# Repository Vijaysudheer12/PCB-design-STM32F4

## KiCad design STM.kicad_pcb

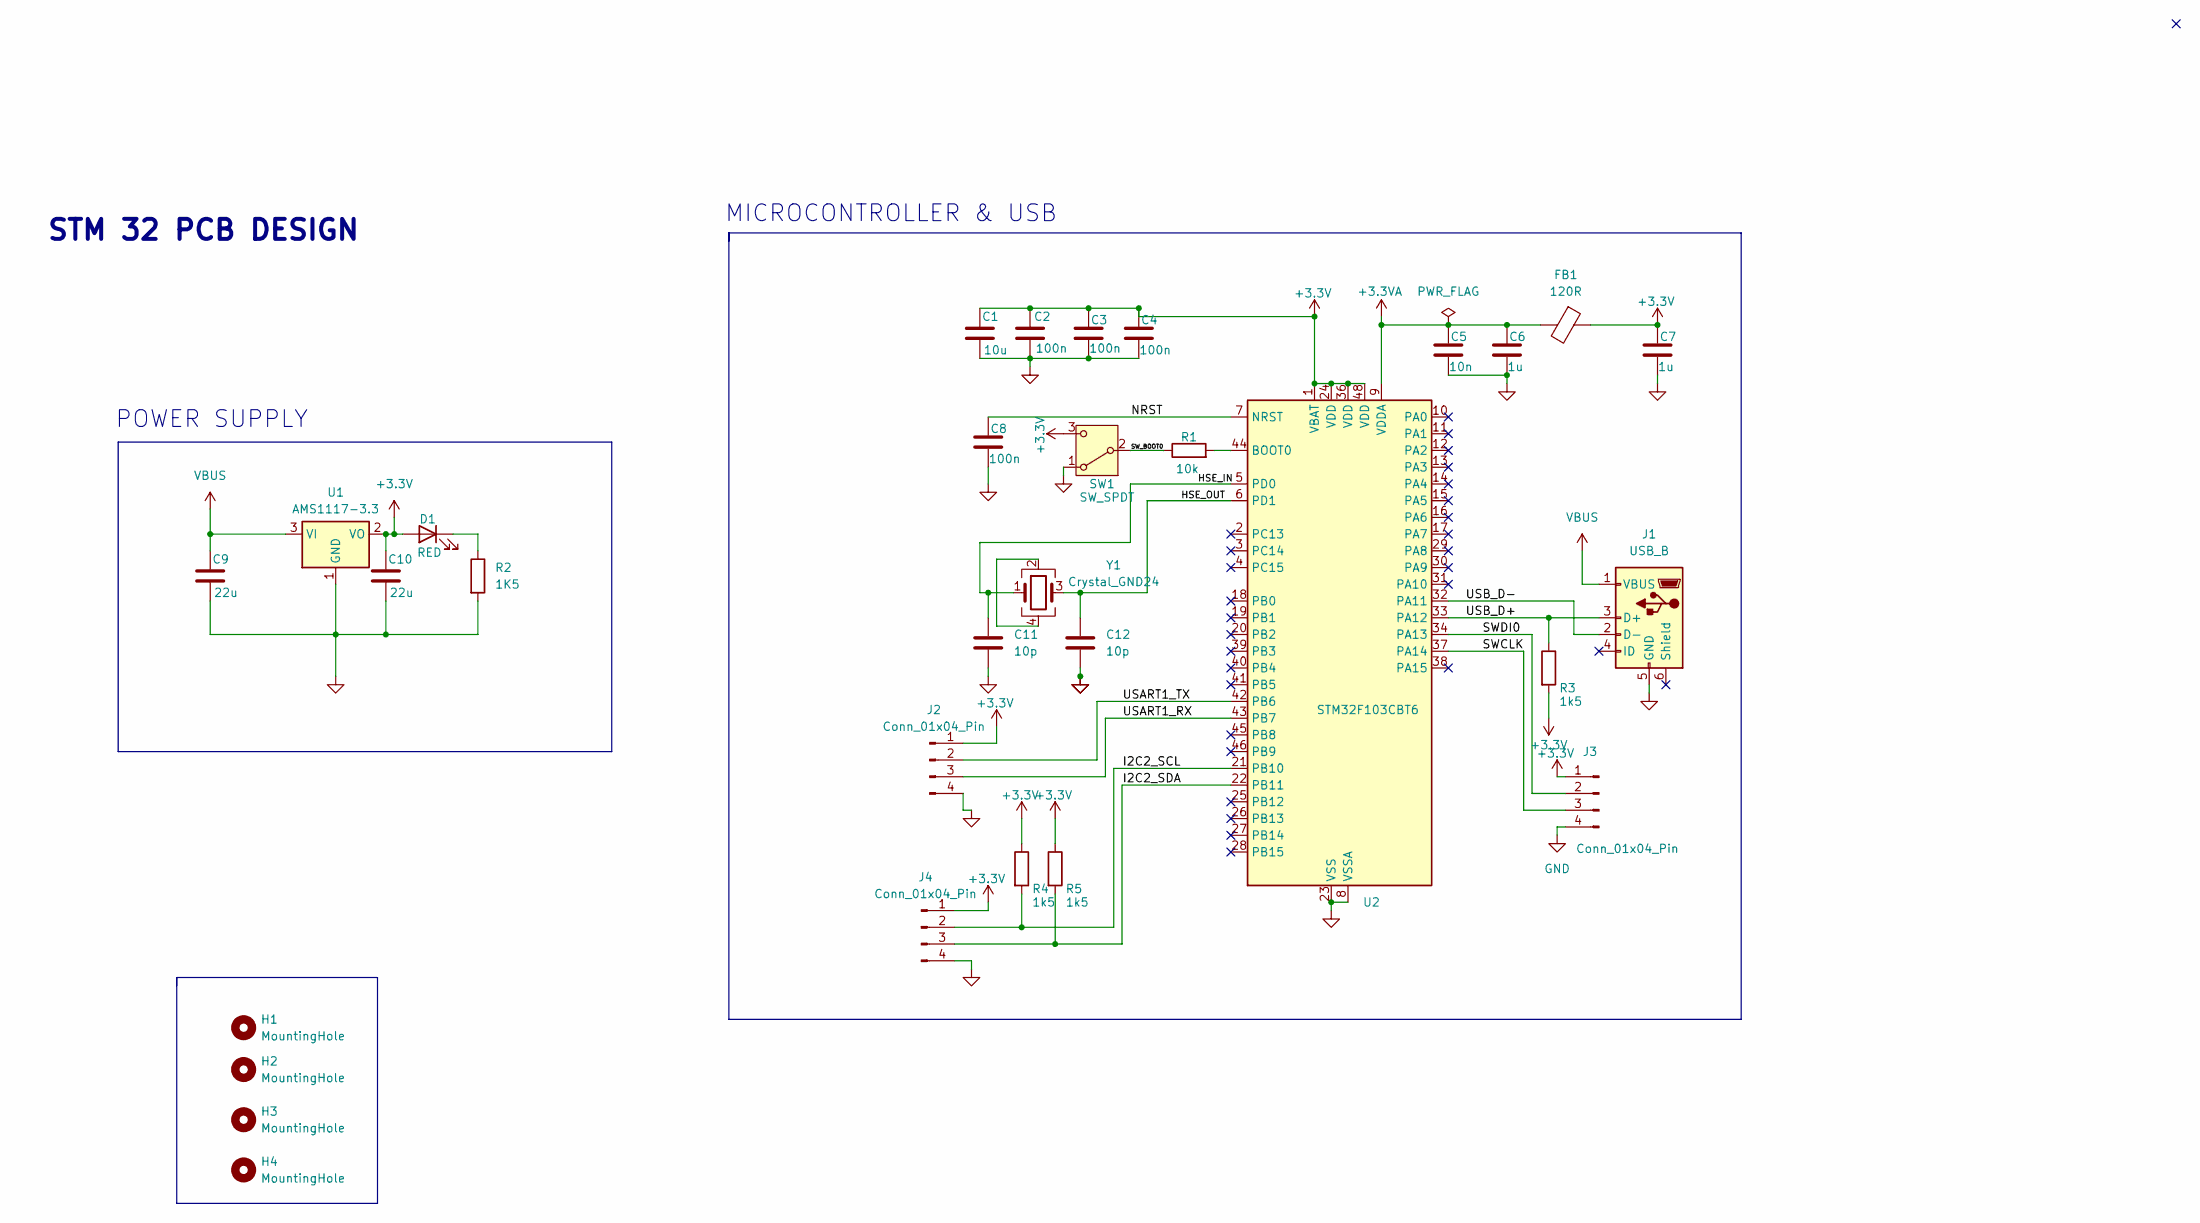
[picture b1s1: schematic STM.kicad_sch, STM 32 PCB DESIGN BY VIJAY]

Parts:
C1: 10u; C_0603_1608Metric
C2, C3, C4, C8: 100n; C_0402_1005Metric
C5: 10n; C_0402_1005Metric
C6, C7: 1u; C_0402_1005Metric
C9, C10: 22u; C_0805_2012Metric
C11, C12: 10p; C_0402_1005Metric
D1: RED; LED_0603_1608Metric
FB1: 120R; L_0603_1608Metric
H1, H2, H3, H4: MountingHole; MountingHole_2.2mm_M2
J1: USB_B; USB_Micro-B_Wuerth_629105150521
J2, J3, J4: Conn_01x04_Pin; PinSocket_1x04_P2.54mm_Vertical
R1: 10k; R_0402_1005Metric
R2: 1K5; R_0402_1005Metric
R3, R4, R5: 1k5; R_0402_1005Metric
SW1: SW_SPDT; SW_SPDT_PCM12
U1: AMS1117-3.3; SOT-223-3_TabPin2
U2: STM32F103CBT6; LQFP-48_7x7mm_P0.5mm
Y1: Crystal_GND24; Crystal_SMD_3225-4Pin_3.2x2.5mm

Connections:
+3.3V: C1.1, C2.1, C3.1, C4.1, C7.1, C10.1, D1.2 (A), FB1.1, J2.1, J3.1, J4.1, R3.2, R4.1, R5.1, SW1.3 (C), U1.2 (VO), U2.1 (VBAT), U2.24 (VDD), U2.36 (VDD), U2.48 (VDD)
+3.3VA: C5.1, C6.1, FB1.2, U2.9 (VDDA)
/HSE_IN: C11.1, U2.5 (PD0), Y1.1
/HSE_OUT: C12.1, U2.6 (PD1), Y1.3
/I2C2_SCL: J4.2, R4.2, U2.21 (PB10)
/I2C2_SDA: J4.3, R5.2, U2.22 (PB11)
/NRST: C8.1, U2.7 (NRST)
/SWCLK: J3.3, U2.37 (PA14)
/SWDI0: J3.2, U2.34 (PA13)
/SW_BOOT0: R1.1, SW1.2 (B)
/USART1_RX: J2.3, U2.43 (PB7)
/USART1_TX: J2.2, U2.42 (PB6)
/USB_D+: J1.3 (D+), R3.1, U2.33 (PA12)
/USB_D-: J1.2 (D-), U2.32 (PA11)
GND: C1.2, C2.2, C3.2, C4.2, C5.2, C6.2, C7.2, C8.2, C9.2, C10.2, C11.2, C12.2, J1.5 (GND), J2.4, J3.4, J4.4, R2.2, SW1.1 (A), U1.1 (GND), U2.8 (VSSA), U2.23 (VSS), U2.35 (VSS), U2.47 (VSS)
unnamed: D1.1 (K), R2.1
unnamed: R1.2, U2.44 (BOOT0)
unnamed: Y1.2, Y1.4
VBUS: C9.1, J1.1 (VBUS), U1.3 (VI)

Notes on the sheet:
MICROCONTROLLER & USB
POWER SUPPLY
STM 32 PCB DESIGN

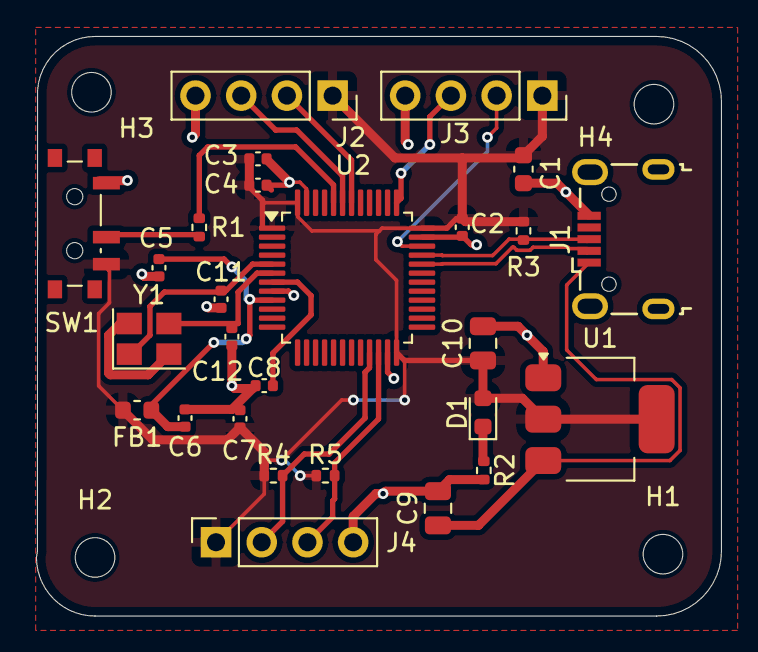
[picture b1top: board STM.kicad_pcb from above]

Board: 2 copper layers, 38.1 x 32.2 mm, 31 parts (0 on the bottom side), 19 nets.
